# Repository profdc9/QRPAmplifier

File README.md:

This is a layout of the WA2EBY amplifier, improved with an added overcurrent circuit protection for the PA transistors.  It is licensed under CC-BY-SA 4.0 by Daniel Marks KW4TI

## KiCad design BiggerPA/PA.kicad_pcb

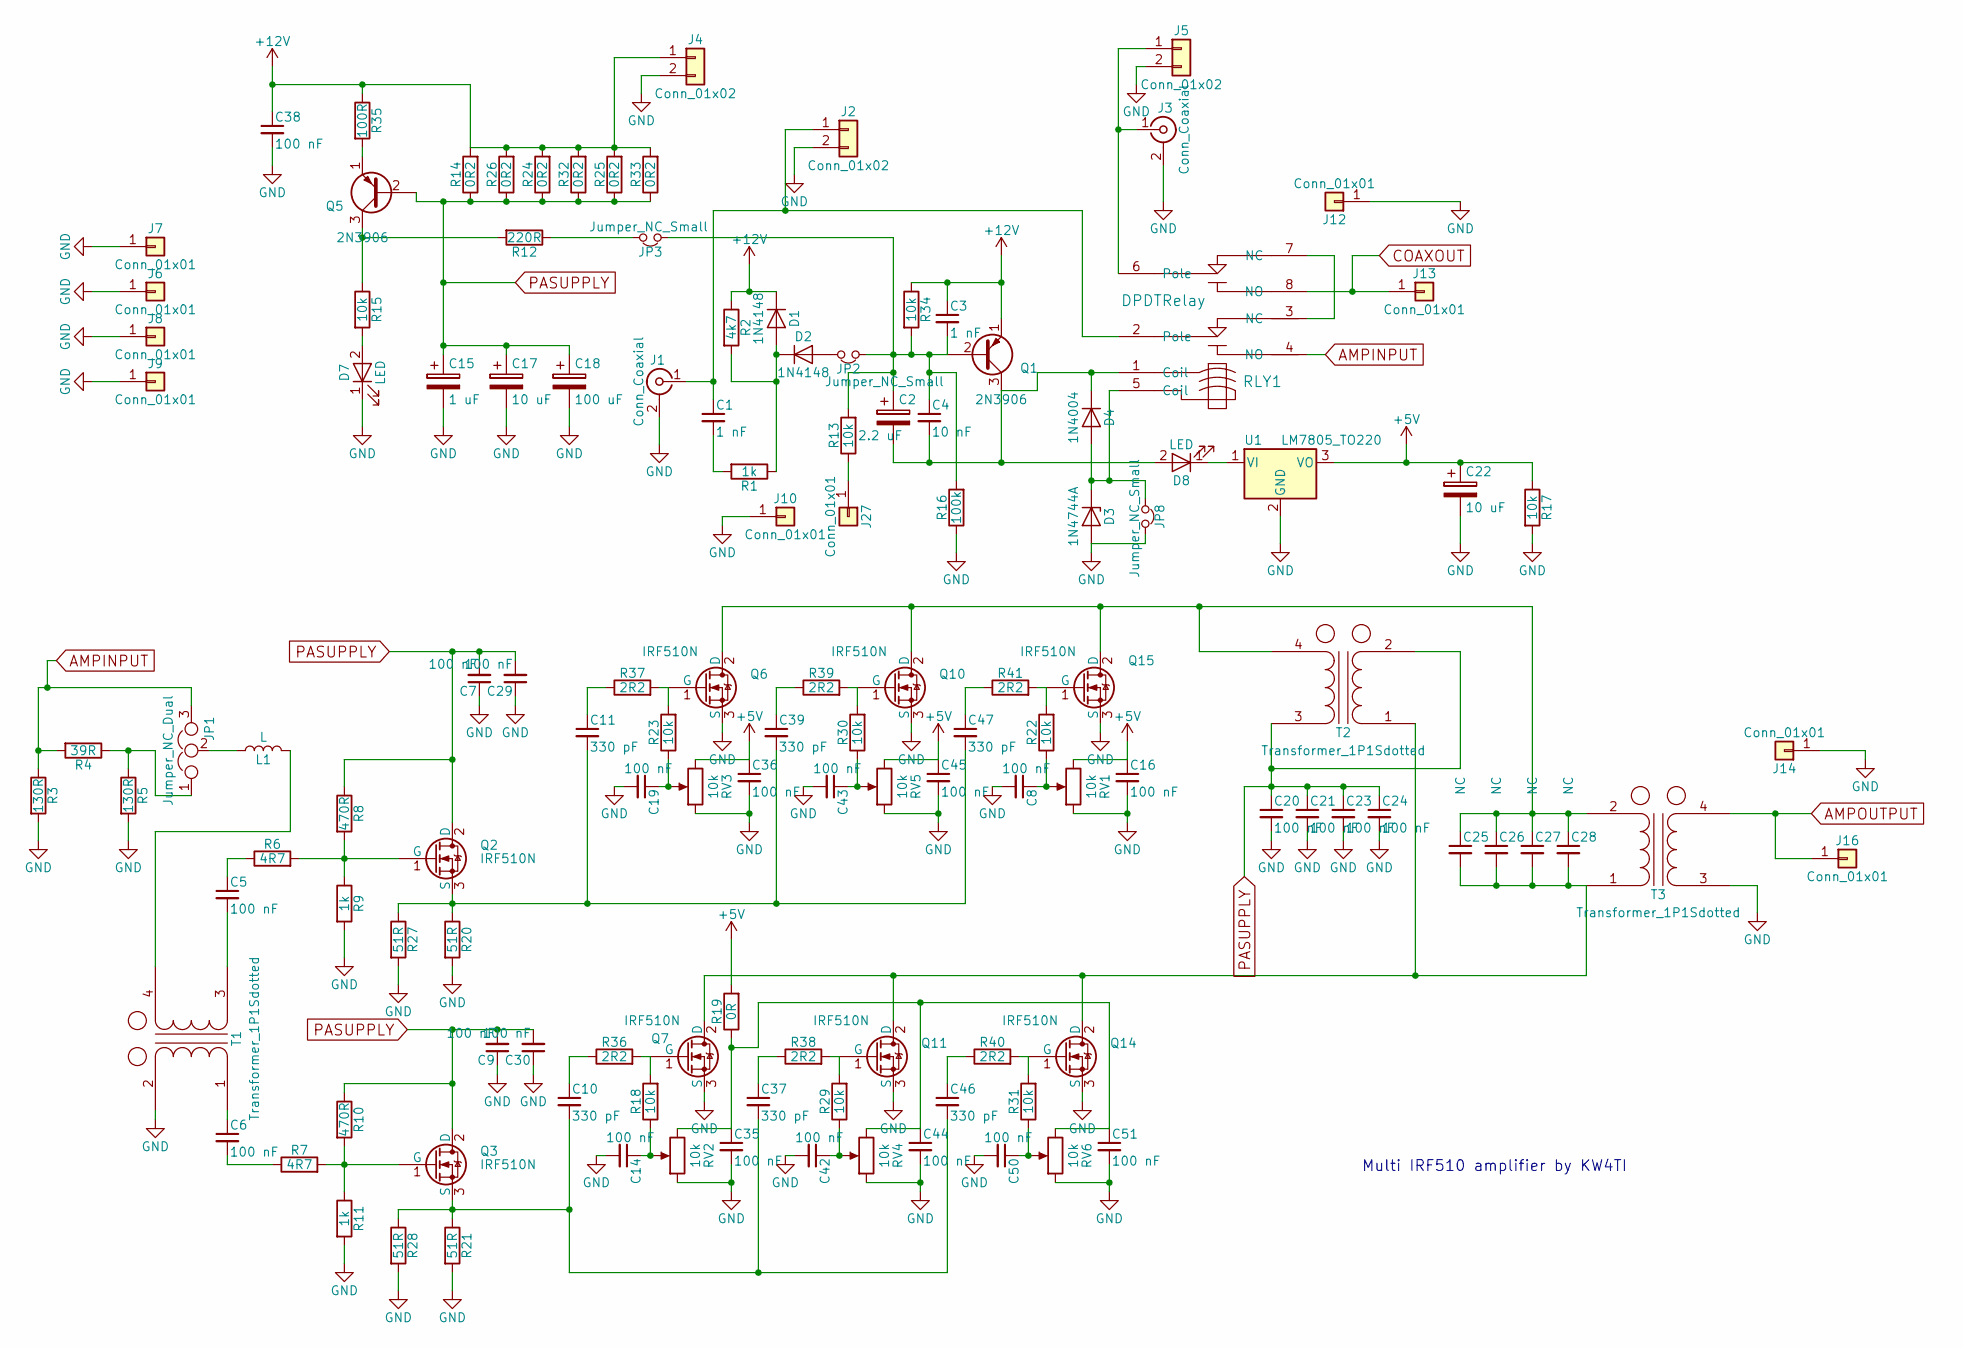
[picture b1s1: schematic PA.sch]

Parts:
C1: 1 nF; C_Disc_D5.0mm_W2.5mm_P5.00mm
C2: 2.2 uF; CP_Radial_D5.0mm_P2.50mm
C3: 1 nF; C_Disc_D5.0mm_W2.5mm_P2.50mm
C4: 10 nF; C_Disc_D5.0mm_W2.5mm_P2.50mm
C5, C6, C20, C21, C23, C24: 100 nF; C_Disc_D5.0mm_W2.5mm_P5.00mm
C7, C8, C9, C14, C16, C19, C29, C30, C35, C36, C38, C42, C43, C44, C45, C50, C51: 100 nF; C_Disc_D5.0mm_W2.5mm_P2.50mm
C10, C11, C37, C39, C46, C47: 330 pF; C_Disc_D5.0mm_W2.5mm_P2.50mm
C15: 1 uF; CP_Radial_D5.0mm_P2.50mm
C17: 10 uF; CP_Radial_D8.0mm_P5.00mm
C18: 100 uF; CP_Radial_D10.0mm_P5.00mm
C22: 10 uF; CP_Radial_D5.0mm_P2.50mm
C25, C26, C27, C28: NC; C_Disc_D5.0mm_W2.5mm_P5.00mm
D1, D2: 1N4148; D_DO-35_SOD27_P7.62mm_Horizontal
D3: 1N4744A; D_DO-41_SOD81_P7.62mm_Horizontal
D4: 1N4004; D_DO-41_SOD81_P7.62mm_Horizontal
D7, D8: LED; LED_D3.0mm
J1, J3: Conn_Coaxial; bnc_90_1-1337543-0
J2, J4, J5: Conn_01x02; TerminalBlock_bornier-2_P5.08mm
J6, J7, J8, J9, J10, J12, J13, J14, J16, J27: Conn_01x01; 1pin
JP1: Jumper_NC_Dual; Pin_Header_Straight_1x03_Pitch2.54mm
JP2, JP3, JP8: Jumper_NC_Small; Pin_Header_Straight_1x02_Pitch2.54mm
L1: L; L_Axial_L6.6mm_D2.7mm_P10.16mm_Horizontal_Vishay_IM-2
Q1, Q5: 2N3906; TO-92_Molded_Narrow
Q2, Q3, Q6, Q7, Q10, Q11, Q14, Q15: IRF510N; TO-220-3_Vertical_WithPads
R1: 1k; R_Axial_DIN0207_L6.3mm_D2.5mm_P7.62mm_Horizontal
R2: 4k7; R_Axial_DIN0207_L6.3mm_D2.5mm_P7.62mm_Horizontal
R3, R5: 130R; R_Axial_DIN0411_L9.9mm_D3.6mm_P12.70mm_Horizontal
R4: 39R; R_Axial_DIN0411_L9.9mm_D3.6mm_P12.70mm_Horizontal
R6, R7: 4R7; R_Axial_DIN0207_L6.3mm_D2.5mm_P10.16mm_Horizontal
R8, R10: 470R; R_Axial_DIN0207_L6.3mm_D2.5mm_P10.16mm_Horizontal
R9, R11: 1k; R_Axial_DIN0207_L6.3mm_D2.5mm_P10.16mm_Horizontal
R12: 220R; R_Axial_DIN0207_L6.3mm_D2.5mm_P7.62mm_Horizontal
R13, R15, R17, R18, R22, R23, R29, R30, R31, R34: 10k; R_Axial_DIN0207_L6.3mm_D2.5mm_P7.62mm_Horizontal
R14, R24, R25, R26, R32, R33: 0R2; R_Axial_DIN0411_L9.9mm_D3.6mm_P12.70mm_Horizontal
R16: 100k; R_Axial_DIN0207_L6.3mm_D2.5mm_P7.62mm_Horizontal
R19: 0R; R_Axial_DIN0207_L6.3mm_D2.5mm_P7.62mm_Horizontal
R20, R21, R27, R28: 51R; R_Axial_DIN0309_L9.0mm_D3.2mm_P12.70mm_Horizontal
R35: 100R; R_Axial_DIN0207_L6.3mm_D2.5mm_P7.62mm_Horizontal
R36, R37, R38, R39, R40, R41: 2R2; R_Axial_DIN0207_L6.3mm_D2.5mm_P10.16mm_Horizontal
RLY1: DPDTRelay; G2VRelay
RV1, RV2, RV3, RV4, RV5, RV6: 10k; Potentiometer_Trimmer_Bourns_3296W
T1, T2: Transformer_1P1Sdotted; GenericCMCL3
T3: Transformer_1P1Sdotted; GenericCMCLCP2
U1: LM7805_TO220; TO-220-3_Vertical

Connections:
+5V: C16.1, C22.1, C36.1, C45.1, R17.1, R19.2, RV1.3, RV3.3, RV5.3, U1.3 (VO)
+12V: C3.1, C38.1, D1.1 (K), J4.1, Q1.1 (E), R2.1, R14.2, R24.2, R25.2, R26.2, R32.2, R33.2, R34.1, R35.1
AMPINPUT: JP1.3, R3.1, R4.2, RLY1.4 (NO)
AMPOUTPUT: J16.1, T3.4 (SB)
COAXOUT: J13.1, RLY1.8 (NO)
GND: C7.1, C8.2, C9.1, C14.2, C15.2, C16.2, C17.2, C18.2, C19.2, C20.2, C21.2, C22.2, C23.2, C24.2, C29.1, C30.1, C35.2, C36.2, C38.2, C42.2, C43.2, C44.2, C45.2, C50.2, C51.2, D3.2 (A), D7.1 (K), J1.2 (Ext), J2.2, J3.2 (Ext), J4.2, J5.2, J6.1, J7.1, J8.1, J9.1, J10.1, J12.1, J14.1, JP8.2, Q6.3 (S), Q7.3 (S), Q10.3 (S), Q11.3 (S), Q14.3 (S), Q15.3 (S), R3.2, R5.2, R9.2, R11.2, R16.1, R17.2, R20.2, R21.2, R27.2, R28.2, RV1.1, RV2.1, RV3.1, RV4.1, RV5.1, RV6.1, T1.2 (AB), T3.3 (SA), U1.2 (GND)
unnamed: C1.1, J1.1 (In), J2.1, RLY1.2 (Pole)
unnamed: C1.2, R1.2
unnamed: C2.1, C3.2, C4.1, JP2.1, JP3.1, Q1.2 (B), R13.2, R16.2, R34.2
unnamed: C2.2, C4.2, D4.1 (K), D8.2 (A), Q1.3 (C), RLY1.1 (Coil)
unnamed: C5.1, R6.1
unnamed: C5.2, T1.3 (SA)
unnamed: C6.1, T1.1 (AA)
unnamed: C6.2, R7.1
unnamed: C8.1, R22.1, RV1.2
unnamed: C10.1, R36.1
unnamed: C10.2, C37.2, C46.2, Q3.3 (S), R21.1, R28.1
unnamed: C11.1, R37.1
unnamed: C11.2, C39.2, C47.2, Q2.3 (S), R20.1, R27.1
unnamed: C14.1, R18.1, RV2.2
unnamed: C19.1, R23.1, RV3.2
unnamed: C25.1, C26.1, C27.1, C28.1, Q6.2 (D), Q10.2 (D), Q15.2 (D), T2.4 (SB), T3.2 (AB)
unnamed: C25.2, C26.2, C27.2, C28.2, Q7.2 (D), Q11.2 (D), Q14.2 (D), T2.1 (AA), T3.1 (AA)
unnamed: C35.1, C44.1, C51.1, R19.1, RV2.3, RV4.3, RV6.3
unnamed: C37.1, R38.1
unnamed: C39.1, R39.1
unnamed: C42.1, R29.1, RV4.2
unnamed: C43.1, R30.1, RV5.2
unnamed: C46.1, R40.1
unnamed: C47.1, R41.1
unnamed: C50.1, R31.1, RV6.2
unnamed: D1.2 (A), D2.1 (K), R1.1, R2.2
unnamed: D2.2 (A), JP2.2
unnamed: D3.1 (K), D4.2 (A), JP8.1, RLY1.5 (Coil)
unnamed: D7.2 (A), R15.2
unnamed: D8.1 (K), U1.1 (VI)
unnamed: J3.1 (In), J5.1, RLY1.6 (Pole)
unnamed: J27.1, R13.1
unnamed: JP1.1, R4.1, R5.1
unnamed: JP1.2, L1.1
unnamed: JP3.2, R12.1
unnamed: L1.2, T1.4 (SB)
unnamed: Q2.1 (G), R6.2, R8.2, R9.1
unnamed: Q3.1 (G), R7.2, R10.2, R11.1
unnamed: Q5.1 (E), R35.2
unnamed: Q5.3 (C), R12.2, R15.1
unnamed: Q6.1 (G), R23.2, R37.2
unnamed: Q7.1 (G), R18.2, R36.2
unnamed: Q10.1 (G), R30.2, R39.2
unnamed: Q11.1 (G), R29.2, R38.2
unnamed: Q14.1 (G), R31.2, R40.2
unnamed: Q15.1 (G), R22.2, R41.2
unnamed: RLY1.3 (NC), RLY1.7 (NC)
PASUPPLY: C7.2, C9.2, C15.1, C17.1, C18.1, C20.1, C21.1, C23.1, C24.1, C29.2, C30.2, Q2.2 (D), Q3.2 (D), Q5.2 (B), R8.1, R10.1, R14.1, R24.1, R25.1, R26.1, R32.1, R33.1, T2.2 (AB), T2.3 (SA)

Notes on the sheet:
Multi IRF510 amplifier by KW4TI

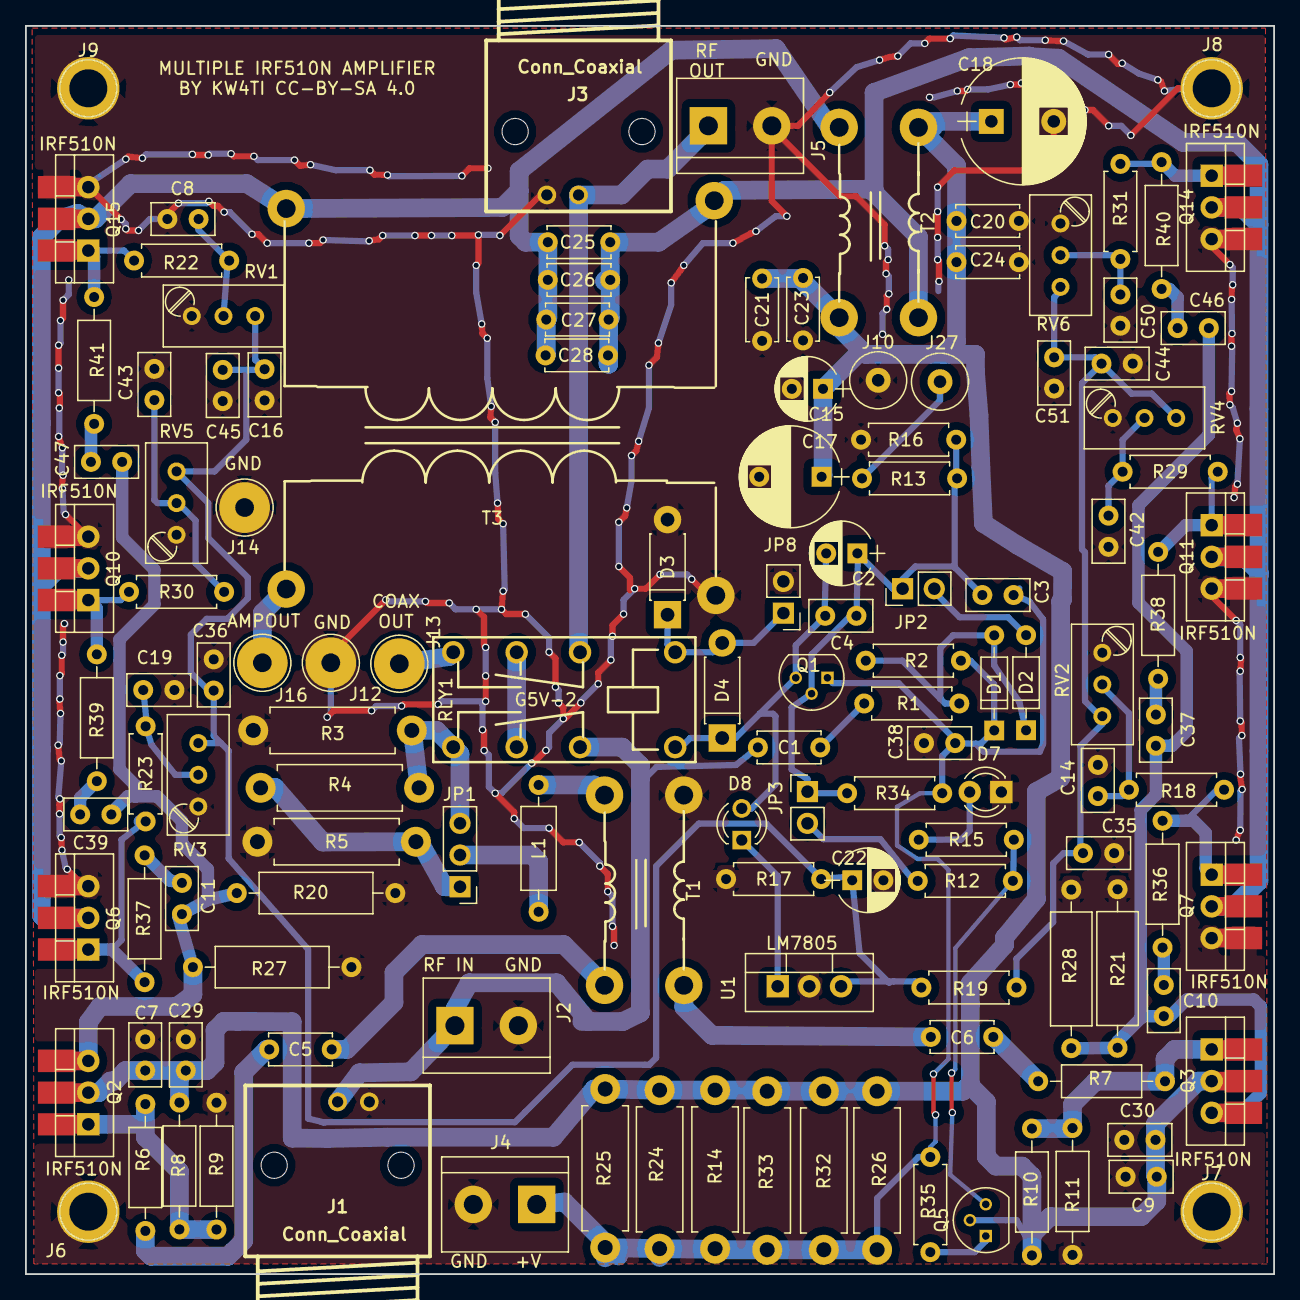
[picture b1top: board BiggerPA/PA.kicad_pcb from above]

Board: 2 copper layers, 100.0 x 100.0 mm, 129 parts (0 on the bottom side), 54 nets.

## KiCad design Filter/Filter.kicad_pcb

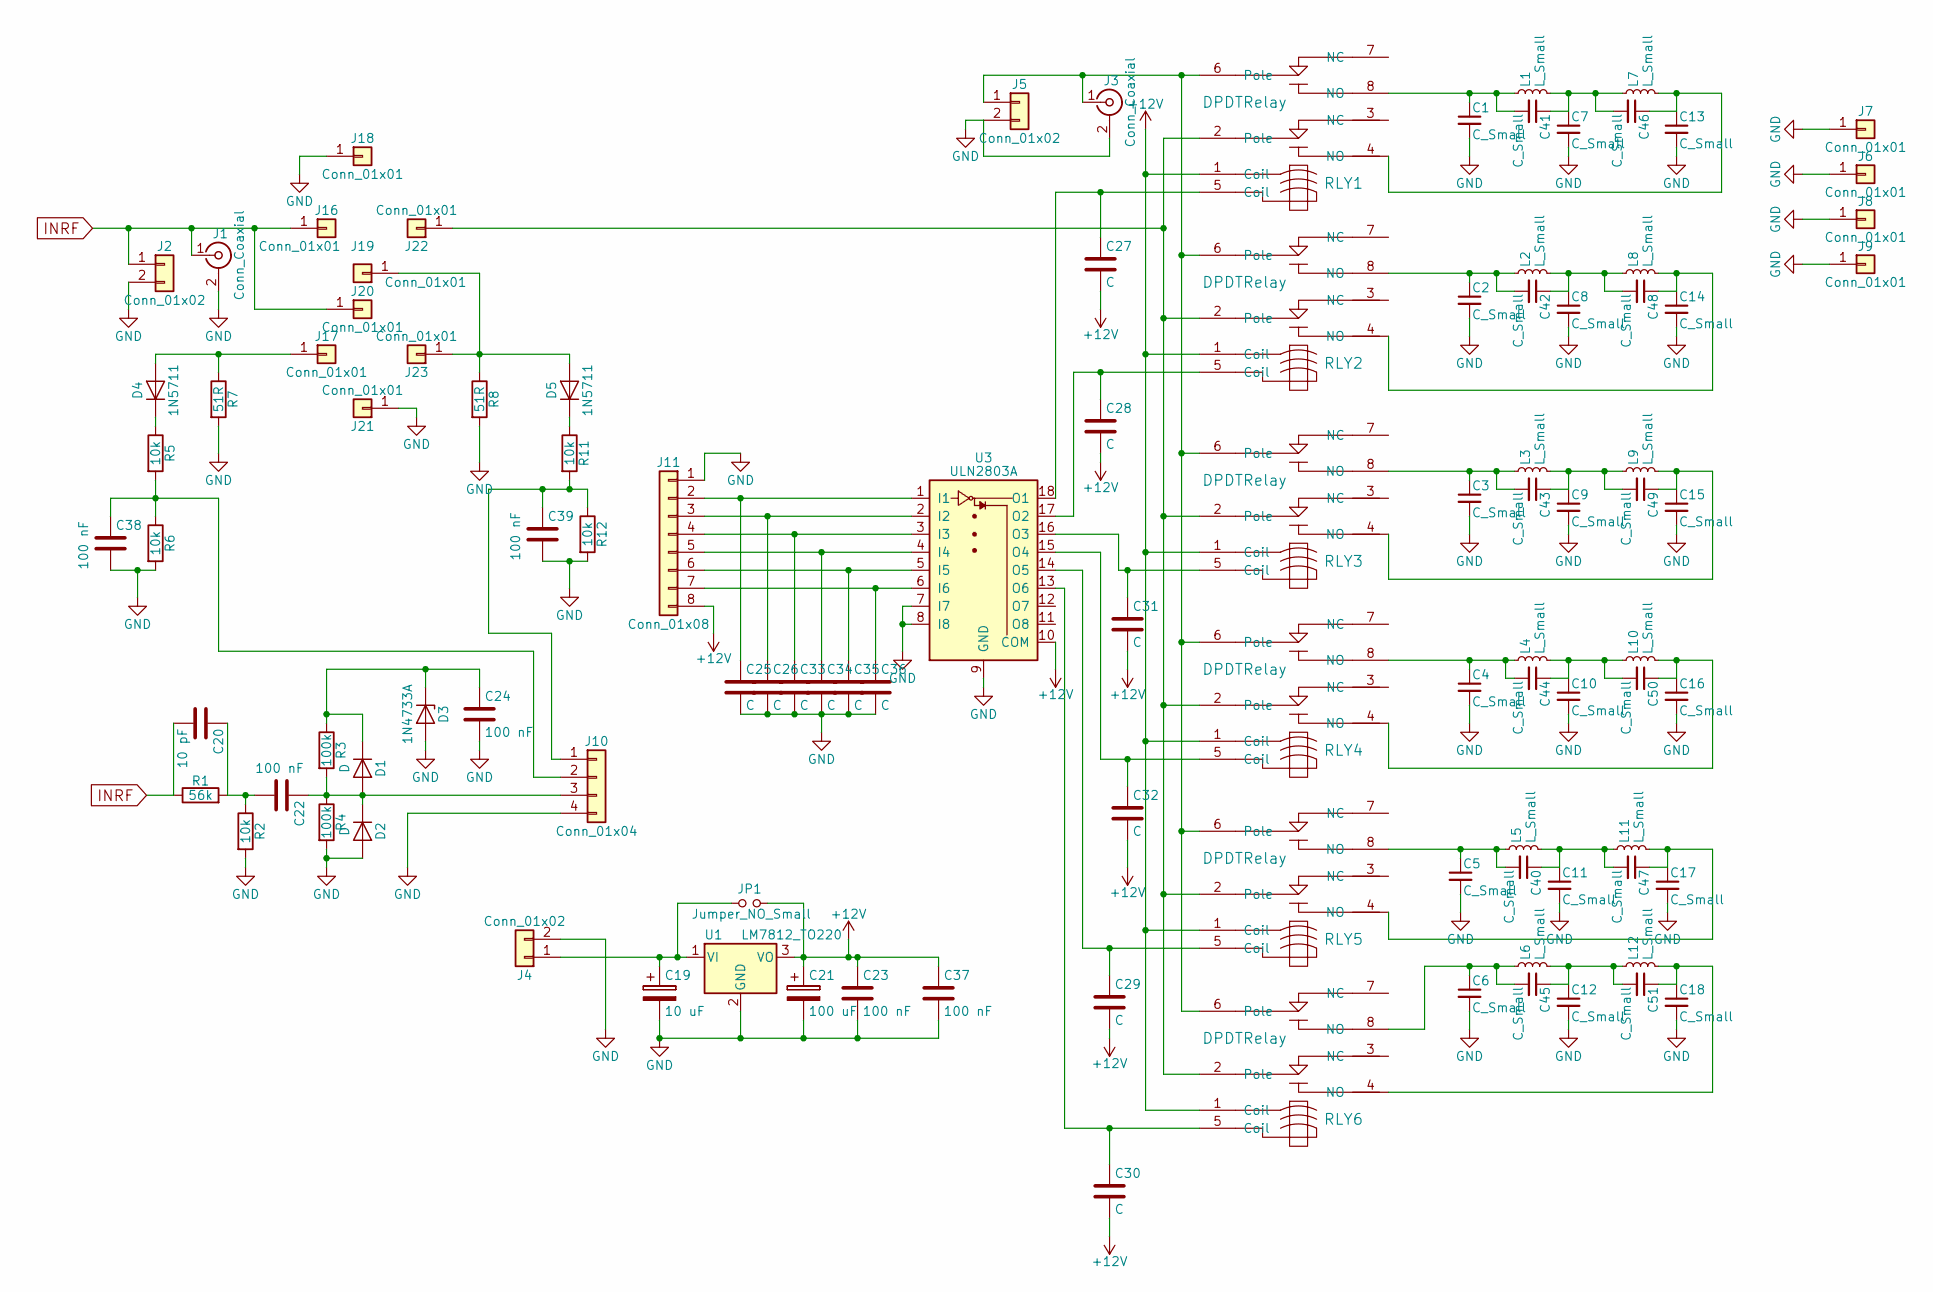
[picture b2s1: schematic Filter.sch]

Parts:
C1, C2, C3, C4, C5, C6, C7, C8, C9, C10, C11, C12, C13, C14, C15, C16, C17, C18, C40, C41, C42, C43, C44, C45, C46, C47, C48, C49, C50, C51: C_Small; C_Disc_SMD
C19: 10 uF; CP_Radial_D6.3mm_P2.50mm
C20: 10 pF; C_Disc_D5.0mm_W2.5mm_P2.50mm
C21: 100 uF; CP_Radial_D6.3mm_P2.50mm
C22, C23, C24, C37, C38, C39: 100 nF; C_Disc_D5.0mm_W2.5mm_P2.50mm
C25, C26, C27, C28, C29, C30, C31, C32, C33, C34, C35, C36: C; C_Disc_D5.0mm_W2.5mm_P2.50mm
D1, D2: D; D_DO-35_SOD27_P7.62mm_Horizontal
D3: 1N4733A; D_DO-41_SOD81_P7.62mm_Horizontal
D4, D5: 1N5711; D_DO-35_SOD27_P7.62mm_Horizontal
J1, J3: Conn_Coaxial; bnc_90_1-1337543-0
J2, J4, J5: Conn_01x02; TerminalBlock_bornier-2_P5.08mm
J6, J7, J8, J9, J16, J17, J18, J19, J20, J21, J22, J23: Conn_01x01; 1pin
J10: Conn_01x04; Molex_KK-6410-04_04x2.54mm_Straight
J11: Conn_01x08; Pin_Header_Straight_1x08_Pitch2.54mm
JP1: Jumper_NO_Small; Pin_Header_Straight_1x02_Pitch2.54mm
L1, L2, L3, L4, L5, L6, L7, L8, L9, L10, L11, L12: L_Small; L_Toroid_Vertical_L13.0mm_W6.5mm_P5.60mm_mod
R1: 56k; R_Axial_DIN0411_L9.9mm_D3.6mm_P15.24mm_Horizontal
R2: 10k; R_Axial_DIN0411_L9.9mm_D3.6mm_P15.24mm_Horizontal
R3, R4: 100k; R_Axial_DIN0207_L6.3mm_D2.5mm_P7.62mm_Horizontal
R5, R6, R11, R12: 10k; R_Axial_DIN0207_L6.3mm_D2.5mm_P7.62mm_Horizontal
R7, R8: 51R; R_Axial_DIN0309_L9.0mm_D3.2mm_P12.70mm_Horizontal
RLY1, RLY2, RLY3, RLY4, RLY5, RLY6: DPDTRelay; G2VRelay
U1: LM7812_TO220; TO-220-3_Vertical
U3: ULN2803A; DIP-18_W7.62mm_Socket

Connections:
+12V: C21.1, C23.1, C27.2, C28.2, C29.2, C30.2, C31.2, C32.2, C37.1, J11.8, JP1.2, RLY1.1 (Coil), RLY2.1 (Coil), RLY3.1 (Coil), RLY4.1 (Coil), RLY5.1 (Coil), RLY6.1 (Coil), U1.3 (VO), U3.10 (COM)
GND: C1.2, C2.2, C3.2, C4.2, C5.2, C6.2, C7.2, C8.2, C9.2, C10.2, C11.2, C12.2, C13.2, C14.2, C15.2, C16.2, C17.2, C18.2, C19.2, C21.2, C23.2, C24.2, C25.2, C26.2, C33.2, C34.2, C35.2, C36.2, C37.2, C38.2, C39.2, D2.2 (A), D3.2 (A), J1.2 (Ext), J2.2, J3.2 (Ext), J4.2, J5.2, J6.1, J7.1, J8.1, J9.1, J10.4, J11.1, J18.1, J21.1, R2.2, R4.2, R6.2, R7.2, R8.2, R12.2, U1.2 (GND), U3.7 (I7), U3.8 (I8), U3.9 (GND)
INRF: C20.2, J1.1 (In), J2.1, J16.1, J20.1, R1.1
unnamed: C1.1, C41.2, L1.1, RLY1.8 (NO)
unnamed: C2.1, C42.2, L2.1, RLY2.8 (NO)
unnamed: C3.1, C43.2, L3.1, RLY3.8 (NO)
unnamed: C4.1, C44.2, L4.1, RLY4.8 (NO)
unnamed: C10.1, C44.1, C50.2, L4.2, L10.1
unnamed: C11.1, C40.1, C47.2, L5.2, L11.1
unnamed: C12.1, C45.1, C51.2, L6.2, L12.1
unnamed: C13.1, C46.1, L7.2, RLY1.4 (NO)
unnamed: C14.1, C48.1, L8.2, RLY2.4 (NO)
unnamed: C15.1, C49.1, L9.2, RLY3.4 (NO)
unnamed: C16.1, C50.1, L10.2, RLY4.4 (NO)
unnamed: C17.1, C47.1, L11.2, RLY5.4 (NO)
unnamed: C18.1, C51.1, L12.2, RLY6.4 (NO)
unnamed: C19.1, J4.1, JP1.1, U1.1 (VI)
unnamed: C20.1, C22.2, R1.2, R2.1
unnamed: C22.1, D1.2 (A), D2.1 (K), J10.3, R3.2, R4.1
unnamed: C24.1, D1.1 (K), D3.1 (K), R3.1
unnamed: C25.1, J11.2, U3.1 (I1)
unnamed: C26.1, J11.3, U3.2 (I2)
unnamed: C27.1, RLY1.5 (Coil), U3.18 (O1)
unnamed: C28.1, RLY2.5 (Coil), U3.17 (O2)
unnamed: C29.1, RLY5.5 (Coil), U3.14 (O5)
unnamed: C30.1, RLY6.5 (Coil), U3.13 (O6)
unnamed: C31.1, RLY3.5 (Coil), U3.16 (O3)
unnamed: C32.1, RLY4.5 (Coil), U3.15 (O4)
unnamed: C33.1, J11.4, U3.3 (I3)
unnamed: C34.1, J11.5, U3.4 (I4)
unnamed: C35.1, J11.6, U3.5 (I5)
unnamed: C36.1, J11.7, U3.6 (I6)
unnamed: C38.1, J10.2, R5.2, R6.1
unnamed: C39.1, J10.1, R11.2, R12.1
unnamed: C5.1, C40.2, L5.1, RLY5.8 (NO)
unnamed: C7.1, C41.1, C46.2, L1.2, L7.1
unnamed: C8.1, C42.1, C48.2, L2.2, L8.1
unnamed: C9.1, C43.1, C49.2, L3.2, L9.1
unnamed: C6.1, C45.2, L6.1, RLY6.8 (NO)
unnamed: D4.1 (K), R5.1
unnamed: D4.2 (A), J17.1, R7.1
unnamed: D5.1 (K), R11.1
unnamed: D5.2 (A), J19.1, J23.1, R8.1
unnamed: J3.1 (In), J5.1, RLY1.6 (Pole), RLY2.6 (Pole), RLY3.6 (Pole), RLY4.6 (Pole), RLY5.6 (Pole), RLY6.6 (Pole)
unnamed: J22.1, RLY1.2 (Pole), RLY2.2 (Pole), RLY3.2 (Pole), RLY4.2 (Pole), RLY5.2 (Pole), RLY6.2 (Pole)

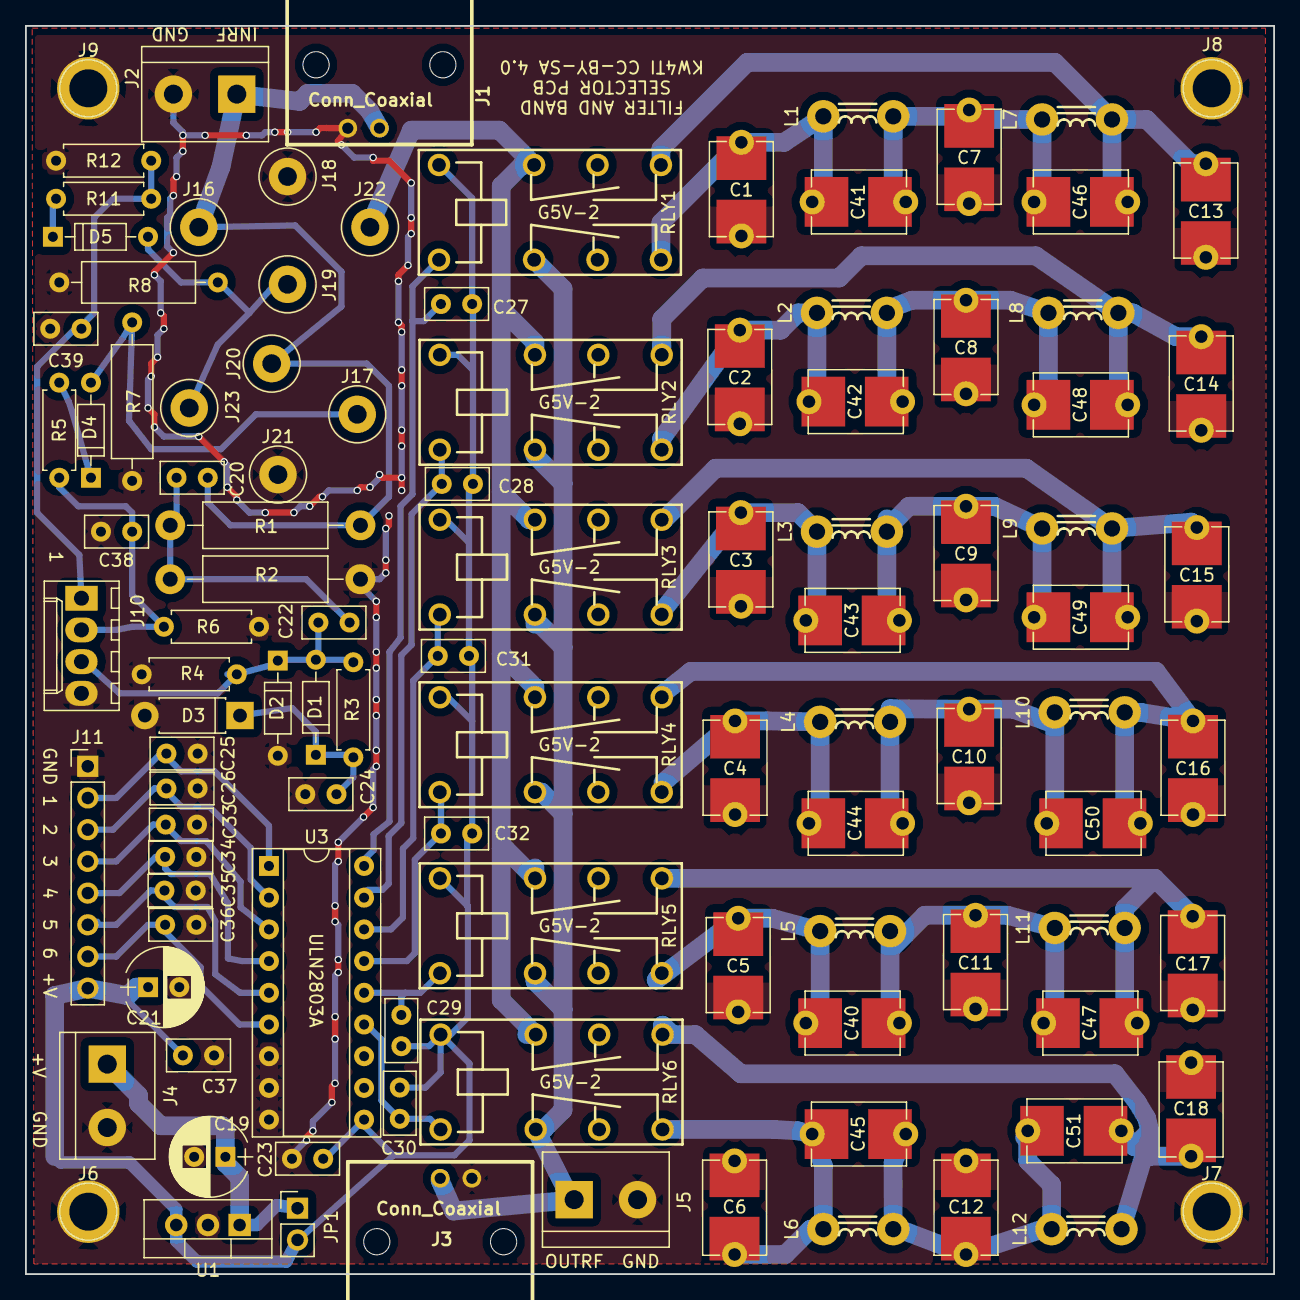
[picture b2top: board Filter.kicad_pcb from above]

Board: 2 copper layers, 100.0 x 100.0 mm, 106 parts (0 on the bottom side), 45 nets.

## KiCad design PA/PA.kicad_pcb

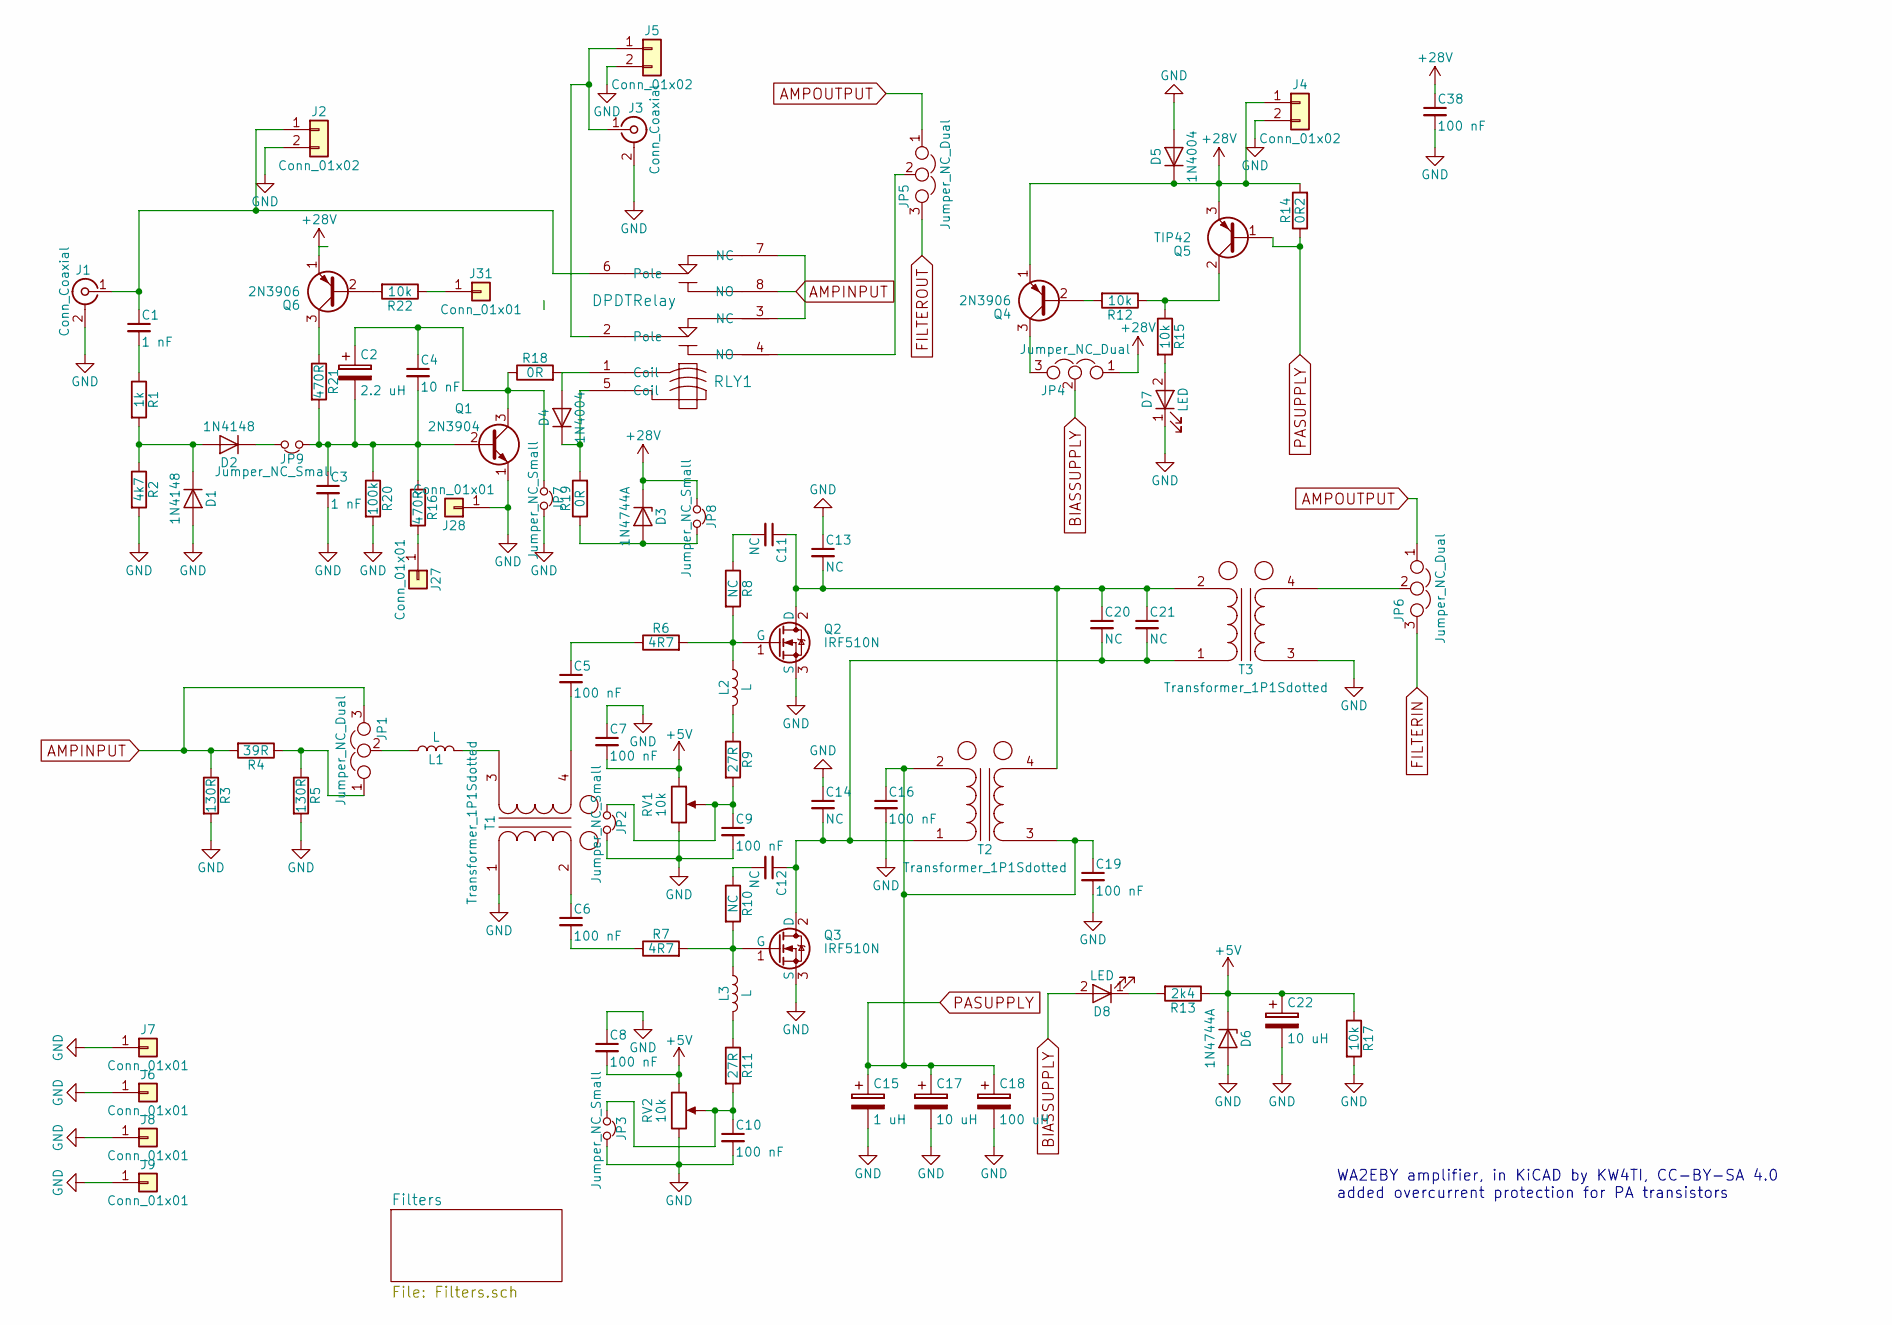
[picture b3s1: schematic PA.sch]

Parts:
C1: 1 nF; C_Disc_D5.0mm_W2.5mm_P5.00mm
C2: 2.2 uH; CP_Radial_D5.0mm_P2.50mm
C3: 1 nF; C_Disc_D5.0mm_W2.5mm_P2.50mm
C4: 10 nF; C_Disc_D5.0mm_W2.5mm_P2.50mm
C5, C6: 100 nF; C_Disc_D5.0mm_W2.5mm_P5.00mm
C7, C8, C9, C10, C16, C19, C38: 100 nF; C_Disc_D5.0mm_W2.5mm_P2.50mm
C11, C12, C13, C14, C20, C21: NC; C_Disc_D5.0mm_W2.5mm_P5.00mm
C15: 1 uH; CP_Radial_D5.0mm_P2.50mm
C17: 10 uH; CP_Radial_D8.0mm_P5.00mm
C18: 100 uH; CP_Radial_D10.0mm_P5.00mm
C22: 10 uH; CP_Radial_D5.0mm_P2.50mm
D1, D2: 1N4148; D_DO-35_SOD27_P7.62mm_Horizontal
D3, D6: 1N4744A; D_DO-41_SOD81_P7.62mm_Horizontal
D4, D5: 1N4004; D_DO-41_SOD81_P7.62mm_Horizontal
D7, D8: LED; LED_D3.0mm
J1, J3: Conn_Coaxial; bnc_90_1-1337543-0
J2, J4, J5: Conn_01x02; TerminalBlock_bornier-2_P5.08mm
J6, J7, J8, J9, J27, J28, J31: Conn_01x01; 1pin
JP1, JP4, JP5, JP6: Jumper_NC_Dual; Pin_Header_Straight_1x03_Pitch2.54mm
JP2, JP3, JP7, JP8, JP9: Jumper_NC_Small; Pin_Header_Straight_1x02_Pitch2.54mm
L1, L2, L3: L; L_Axial_L6.6mm_D2.7mm_P10.16mm_Horizontal_Vishay_IM-2
Q1: 2N3904; TO-92_Molded_Narrow
Q2, Q3: IRF510N; TO-220-3_Vertical_WithPads
Q4, Q6: 2N3906; TO-92_Molded_Narrow
Q5: TIP42; TO-220-3_Vertical_WithPads
R1: 1k; R_Axial_DIN0207_L6.3mm_D2.5mm_P7.62mm_Horizontal
R2: 4k7; R_Axial_DIN0207_L6.3mm_D2.5mm_P7.62mm_Horizontal
R3, R5: 130R; R_Axial_DIN0411_L9.9mm_D3.6mm_P12.70mm_Horizontal
R4: 39R; R_Axial_DIN0411_L9.9mm_D3.6mm_P12.70mm_Horizontal
R6, R7: 4R7; R_Axial_DIN0207_L6.3mm_D2.5mm_P10.16mm_Horizontal
R8, R10: NC; R_Axial_DIN0207_L6.3mm_D2.5mm_P10.16mm_Horizontal
R9, R11: 27R; R_Axial_DIN0207_L6.3mm_D2.5mm_P10.16mm_Horizontal
R12, R15, R17, R22: 10k; R_Axial_DIN0207_L6.3mm_D2.5mm_P7.62mm_Horizontal
R13: 2k4; R_Axial_DIN0411_L9.9mm_D3.6mm_P12.70mm_Horizontal
R14: 0R2; R_Axial_DIN0411_L9.9mm_D3.6mm_P12.70mm_Horizontal
R16, R21: 470R; R_Axial_DIN0207_L6.3mm_D2.5mm_P7.62mm_Horizontal
R18, R19: 0R; R_Axial_DIN0207_L6.3mm_D2.5mm_P7.62mm_Horizontal
R20: 100k; R_Axial_DIN0207_L6.3mm_D2.5mm_P7.62mm_Horizontal
RLY1: DPDTRelay; G2VRelay
RV1, RV2: 10k; Potentiometer_Trimmer_Bourns_3296W
T1, T2: Transformer_1P1Sdotted; GenericCMCL2
T3: Transformer_1P1Sdotted; GenericCMCLCP

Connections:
+5V: C7.2, C8.2, C22.1, D6.1 (K), R13.1, R17.1, RV1.1, RV2.1
+28V: C38.1, D3.1 (K), D5.1 (K), J4.1, JP4.1, JP8.1, Q4.1 (E), Q5.3 (E), Q6.1 (E), R14.2
AMPINPUT: JP1.3, R3.1, R4.2, RLY1.8 (NO)
AMPOUTPUT: JP5.1, JP6.1
BIASSUPPLY: D8.2 (A), JP4.2
FILTERIN: JP6.3; also elsewhere on the board
FILTEROUT: JP5.3; also elsewhere on the board
GND: C3.2, C7.1, C8.1, C9.2, C10.2, C13.1, C14.1, C15.2, C16.2, C17.2, C18.2, C19.2, C22.2, C38.2, D1.2 (A), D5.2 (A), D6.2 (A), D7.1 (K), J1.2 (Ext), J2.2, J3.2 (Ext), J4.2, J5.2, J6.1, J7.1, J8.1, J9.1, J28.1, JP2.2, JP3.2, JP7.2, Q1.1 (E), Q2.3 (S), Q3.3 (S), R2.2, R3.2, R5.2, R17.2, R20.2, RV1.3, RV2.3, T1.1 (AA), T3.3 (SA); also elsewhere on the board
unnamed: C1.1, J1.1 (In), J2.1, RLY1.6 (Pole)
unnamed: C1.2, R1.1
unnamed: C2.1, C4.1, JP7.1, Q1.3 (C), R18.1
unnamed: C2.2, C3.1, C4.2, JP9.1, Q1.2 (B), R16.1, R20.1, R21.2
unnamed: C5.1, R6.1
unnamed: C5.2, T1.4 (SB)
unnamed: C6.1, T1.2 (AB)
unnamed: C6.2, R7.1
unnamed: C9.1, JP2.1, R9.2, RV1.2
unnamed: C10.1, JP3.1, R11.2, RV2.2
unnamed: C11.1, C13.2, C20.1, C21.1, Q2.2 (D), T2.4 (SB), T3.2 (AB)
unnamed: C11.2, R8.1
unnamed: C12.1, C14.2, C20.2, C21.2, Q3.2 (D), T2.1 (AA), T3.1 (AA)
unnamed: C12.2, R10.1
unnamed: D1.1 (K), D2.2 (A), R1.2, R2.1
unnamed: D2.1 (K), JP9.2
unnamed: D3.2 (A), JP8.2, R19.1
unnamed: D4.1 (K), R19.2, RLY1.5 (Coil)
unnamed: D4.2 (A), R18.2, RLY1.1 (Coil)
unnamed: D7.2 (A), R15.2
unnamed: D8.1 (K), R13.2
unnamed: J3.1 (In), J5.1, RLY1.2 (Pole)
unnamed: J27.1, R16.2
unnamed: J31.1, R22.1
unnamed: JP1.1, R4.1, R5.1
unnamed: JP1.2, L1.1
unnamed: JP4.3, Q4.3 (C)
unnamed: JP5.2, RLY1.4 (NO)
unnamed: JP6.2, T3.4 (SB)
unnamed: L1.2, T1.3 (SA)
unnamed: L2.1, Q2.1 (G), R6.2, R8.2
unnamed: L2.2, R9.1
unnamed: L3.1, Q3.1 (G), R7.2, R10.2
unnamed: L3.2, R11.1
unnamed: Q4.2 (B), R12.2
unnamed: Q5.2 (C), R12.1, R15.1
unnamed: Q6.2 (B), R22.2
unnamed: Q6.3 (C), R21.1
unnamed: RLY1.3 (NC), RLY1.7 (NC)
PASUPPLY: C15.1, C16.1, C17.1, C18.1, C19.1, Q5.1 (B), R14.1, T2.2 (AB), T2.3 (SA)

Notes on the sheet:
WA2EBY amplifier, in KiCAD by KW4TI, CC-BY-SA 4.0 added overcurrent protection for PA transistors

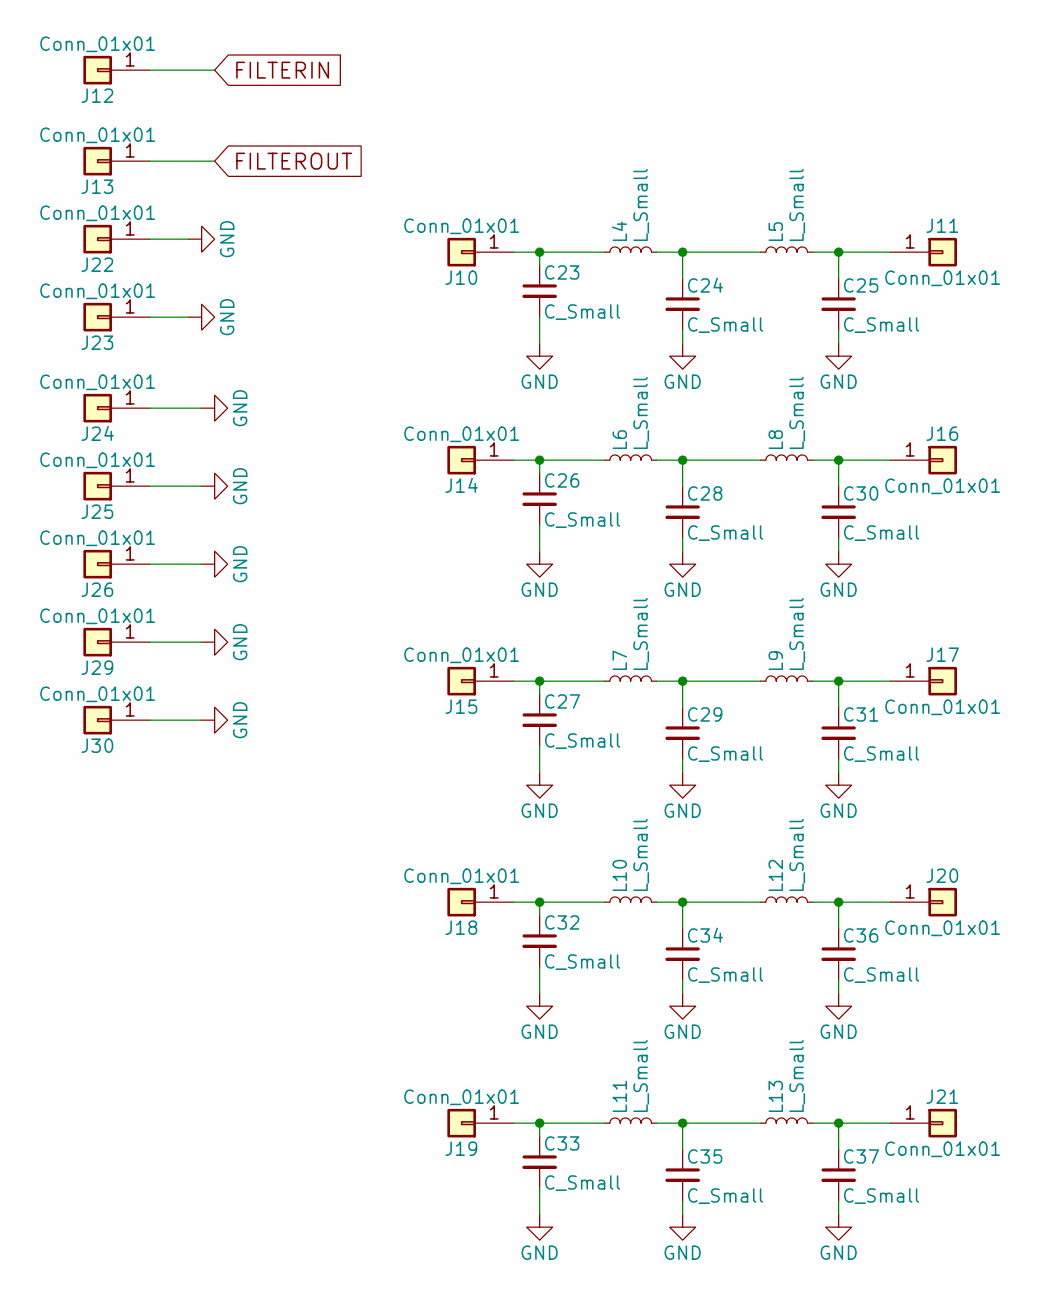
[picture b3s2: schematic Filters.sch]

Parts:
C23, C24, C25, C26, C27, C28, C29, C30, C31, C32, C33, C34, C35, C36, C37: C_Small; C_Disc_SMD
J10, J11, J12, J13, J14, J15, J16, J17, J18, J19, J20, J21, J22, J23, J24, J25, J26, J29, J30: Conn_01x01; 1pin
L4, L5, L6, L7, L8, L9, L10, L11, L12, L13: L_Small; L_Toroid_Vertical_L13.0mm_W6.5mm_P5.60mm

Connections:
FILTERIN: J12.1; also elsewhere on the board
FILTEROUT: J13.1; also elsewhere on the board
GND: C23.2, C24.2, C25.2, C26.2, C27.2, C28.2, C29.2, C30.2, C31.2, C32.2, C33.2, C34.2, C35.2, C36.2, C37.2, J22.1, J23.1, J24.1, J25.1, J26.1, J29.1, J30.1; also elsewhere on the board
unnamed: C23.1, J10.1, L4.1
unnamed: C24.1, L4.2, L5.1
unnamed: C25.1, J11.1, L5.2
unnamed: C26.1, J14.1, L6.1
unnamed: C27.1, J15.1, L7.1
unnamed: C28.1, L6.2, L8.1
unnamed: C29.1, L7.2, L9.1
unnamed: C30.1, J16.1, L8.2
unnamed: C31.1, J17.1, L9.2
unnamed: C32.1, J18.1, L10.1
unnamed: C33.1, J19.1, L11.1
unnamed: C34.1, L10.2, L12.1
unnamed: C35.1, L11.2, L13.1
unnamed: C36.1, J20.1, L12.2
unnamed: C37.1, J21.1, L13.2
